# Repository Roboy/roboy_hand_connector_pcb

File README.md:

# roboy_hand_connector_pcb
pcb connector board for roboy 2.0 hand rev 1

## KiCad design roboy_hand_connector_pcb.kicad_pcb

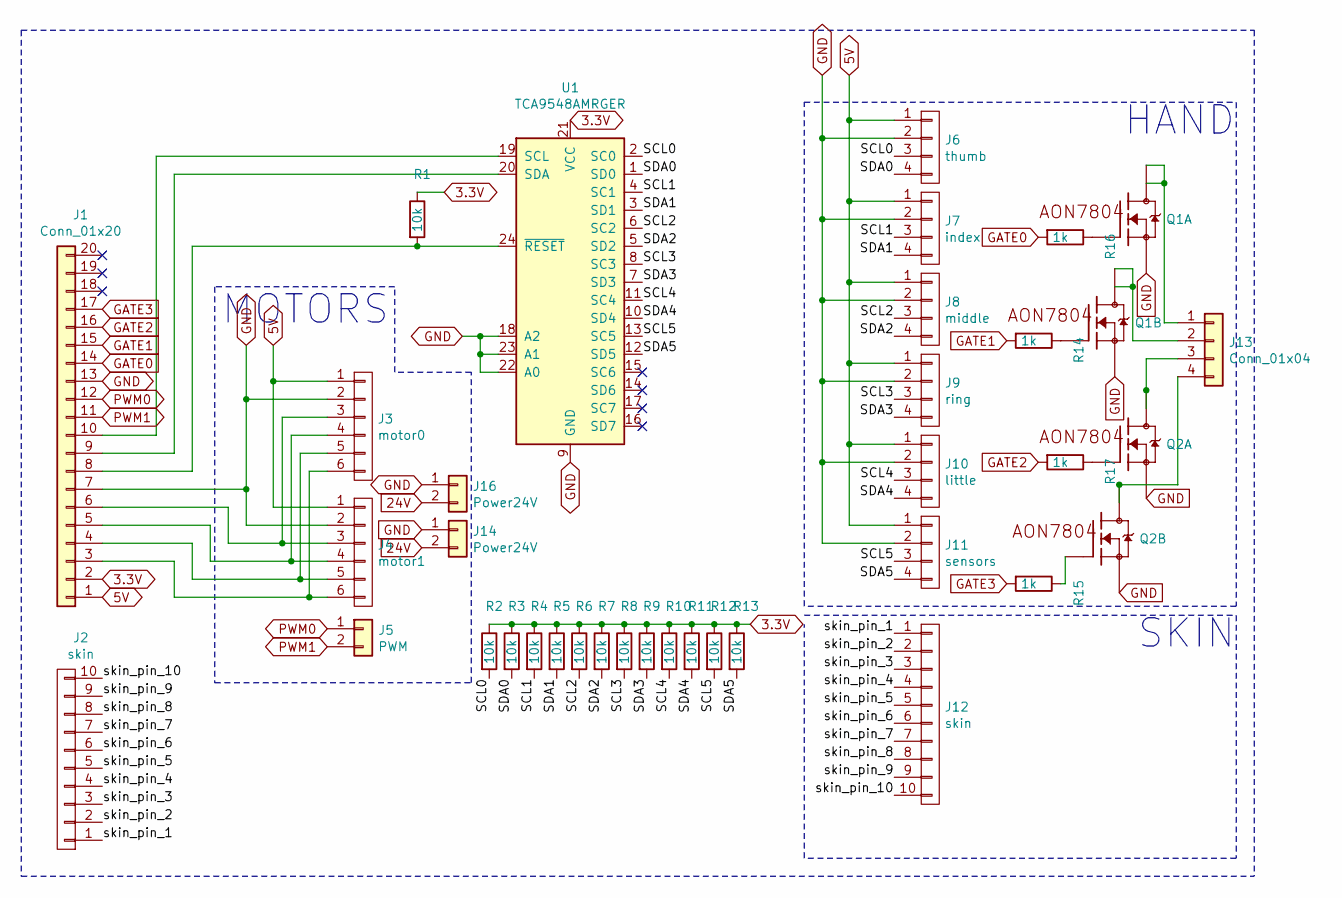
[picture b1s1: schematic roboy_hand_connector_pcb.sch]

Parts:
J1: Conn_01x20; TE-Connectivity_Micro-Match_connector_02x10_Pitch_1.27mm
J2: skin; FPC_0.5mmx10
J3: motor0; TE-Connectivity_Micro-Match_connector_02x03_Pitch_1.27mm
J4: motor1; TE-Connectivity_Micro-Match_connector_02x03_Pitch_1.27mm
J5: PWM; Pin_Header_Straight_1x02_Pitch2.54mm
J6: thumb; TE-Connectivity_Micro-Match_connector_02x02_Pitch_1.27mm
J7: index; TE-Connectivity_Micro-Match_connector_02x02_Pitch_1.27mm
J8: middle; TE-Connectivity_Micro-Match_connector_02x02_Pitch_1.27mm
J9: ring; TE-Connectivity_Micro-Match_connector_02x02_Pitch_1.27mm
J10: little; TE-Connectivity_Micro-Match_connector_02x02_Pitch_1.27mm
J11: sensors; TE-Connectivity_Micro-Match_connector_02x02_Pitch_1.27mm
J12: skin; TE-Connectivity_Micro-Match_connector_02x05_Pitch_1.27mm
J13: Conn_01x04; TE-Connectivity_Micro-Match_connector_02x02_Pitch_1.27mm
J14, J16: Power24V; Wago_2060_2_SMD
Q1, Q2: AON7804; DFN3X3
R1, R2, R3, R4, R5, R6, R7, R8, R9, R10, R11, R12, R13: 10k; R_0402
R14, R15, R16, R17: 1k; R_0402
U1: TCA9548AMRGER; QFN-24-1EP_4x4mm_P0.5mm_EP2.6x2.6mm

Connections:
3.3V: J1.2, R1.1, R2.1, R3.1, R4.1, R5.1, R6.1, R7.1, R8.1, R9.1, R10.1, R11.1, R12.1, R13.1, U1.21 (VCC)
5V: J1.1, J3.1, J4.1, J6.1, J7.1, J8.1, J9.1, J10.1, J11.1
24V: J14.2, J16.2
/SCL0: J6.3, R2.2, U1.2 (SC0)
/SCL1: J7.3, R4.2, U1.4 (SC1)
/SCL2: J8.3, R6.2, U1.6 (SC2)
/SCL3: J9.3, R8.2, U1.8 (SC3)
/SCL4: J10.3, R10.2, U1.11 (SC4)
/SCL5: J11.3, R12.2, U1.13 (SC5)
/SDA0: J6.4, R3.2, U1.1 (SD0)
/SDA1: J7.4, R5.2, U1.3 (SD1)
/SDA2: J8.4, R7.2, U1.5 (SD2)
/SDA3: J9.4, R9.2, U1.7 (SD3)
/SDA4: J10.4, R11.2, U1.10 (SD4)
/SDA5: J11.4, R13.2, U1.12 (SD5)
/skin_pin_1: J2.1, J12.1
/skin_pin_2: J2.2, J12.2
/skin_pin_3: J2.3, J12.3
/skin_pin_4: J2.4, J12.4
/skin_pin_5: J2.5, J12.5
/skin_pin_6: J2.6, J12.6
/skin_pin_7: J2.7, J12.7
/skin_pin_8: J2.8, J12.8
/skin_pin_9: J2.9, J12.9
/skin_pin_10: J2.10, J12.10
GATE0: J1.14, R16.2
GATE1: J1.15, R14.2
GATE2: J1.16, R17.2
GATE3: J1.17, R15.2
GND: J1.7, J1.13, J3.2, J4.2, J6.2, J7.2, J8.2, J9.2, J10.2, J11.2, J14.1, J16.1, Q1.S1 (S), Q1.S2 (S), Q2.S1 (S), Q2.S2 (S), U1.9 (GND), U1.18 (A2), U1.22 (A0), U1.23 (A1)
unnamed: J1.3, J3.6, J4.6
unnamed: J1.4, J3.5, J4.5
unnamed: J1.5, J3.4, J4.4
unnamed: J1.6, J3.3, J4.3
unnamed: J1.8, R1.2, U1.24 (~RESET)
unnamed: J1.9, U1.20 (SDA)
unnamed: J1.10, U1.19 (SCL)
unnamed: J13.1, Q1.D1 (D), Q1.D1A (D1)
unnamed: J13.2, Q1.D2 (D), Q1.D2A (D1)
unnamed: J13.3, Q2.D1 (D), Q2.D1A (D1)
unnamed: J13.4, Q2.D2 (D), Q2.D2A (D1)
unnamed: Q1.G1 (G), R16.1
unnamed: Q1.G2 (G), R14.1
unnamed: Q2.G1 (G), R17.1
unnamed: Q2.G2 (G), R15.1
PWM0: J1.12, J5.1
PWM1: J1.11, J5.2

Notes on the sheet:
SKIN
MOTORS
HAND

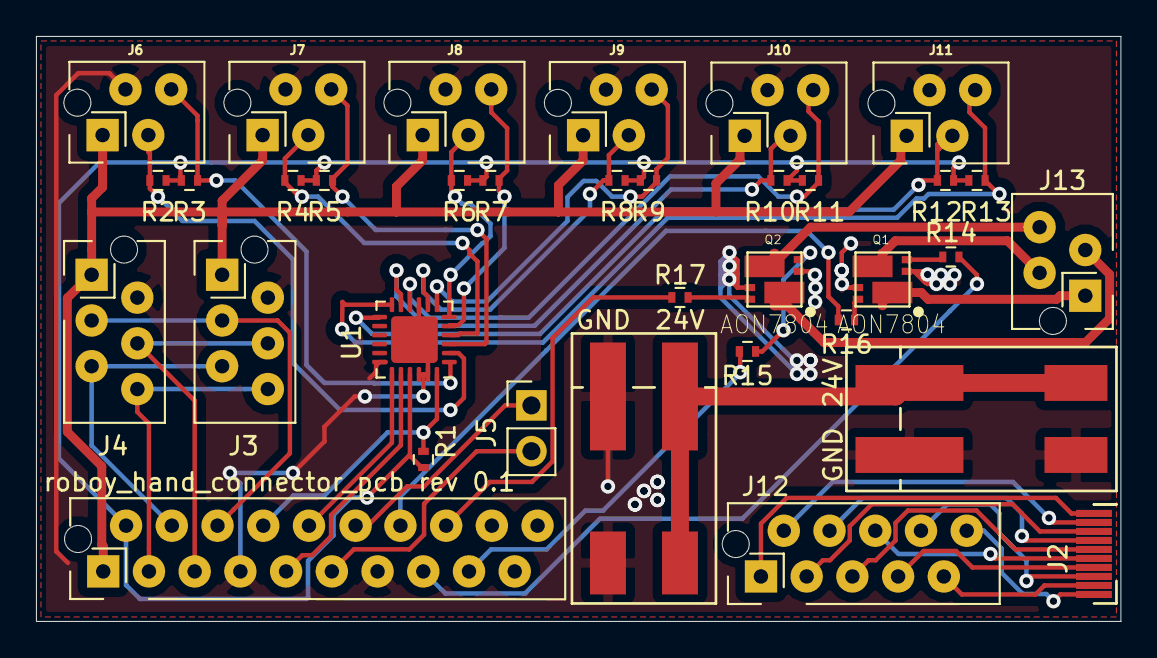
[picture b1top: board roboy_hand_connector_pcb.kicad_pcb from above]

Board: 2 copper layers, 60.2 x 32.5 mm, 35 parts (0 on the bottom side), 47 nets.

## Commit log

2019-01-18 initial
2019-01-21 i2c buses, spi bus and skin done schematics
2019-01-28 with schematics done
2019-01-28 layout draft
2019-01-28 layout done
2019-01-28 connect the unconnected
2019-01-29 rev 0.1
2019-01-29 aisler order ready
2019-02-12 with vidor shield draft
2019-02-12 with board step
